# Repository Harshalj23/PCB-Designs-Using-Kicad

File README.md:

# KiCad Projects – Embedded & IoT Hardware Designs

This repository contains a collection of my hardware design projects created using **KiCad**, focused on embedded systems and IoT applications.  
These projects reflect my practical experience in schematic design, PCB layout, and hardware–software integration.

---

## 🛠 Tools & Technologies
- **EDA Tool:** KiCad
- **Microcontrollers:** ESP32, STM32
- **Design Areas:** PCB Design, Schematic Capture, Embedded Hardware
- **Protocols:** UART, SPI, I2C, MQTT, HTTP

---

## 📂 Projects Included
Each folder in this repository represents a complete KiCad project, including schematics, PCB layouts, and supporting files.

Examples:
- **Power Supply Board**
- **IoT Sensor Node**
- **Motor Driver Module**

---

## 🎯 Objectives
- Practice and improve professional PCB design workflow
- Build real-world embedded hardware
- Maintain a clean hardware project portfolio

---

## 🧪 Status
These designs are part of my continuous learning and development in the embedded & IoT domain.  
Updates and improvements are added regularly.

---

## 📬 Contact
**Harshal Jaiswal**  
IoT & Embedded Systems Engineer  
📧 harshaljaiswal055@gmail.com  
🔗 [LinkedIn](https://linkedin.com/in/harshalj67)  
🔗 [GitHub](https://github.com/Harshalj23)

---

Feel free to explore, review, or suggest improvements.

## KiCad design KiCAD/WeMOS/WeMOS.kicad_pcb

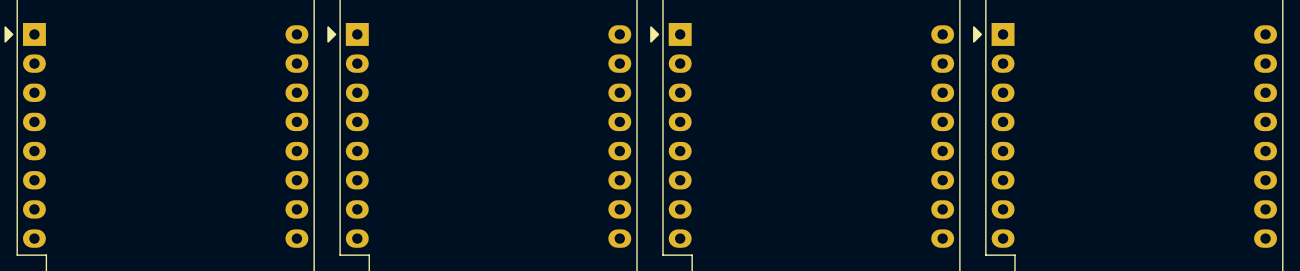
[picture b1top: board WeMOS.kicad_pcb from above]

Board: 2 copper layers, 4 parts (0 on the bottom side), 16 nets, no tracks yet.

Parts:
U1, U2, U3, U4: WEMOS_D1_mini; WEMOS_D1_mini_light

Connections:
unnamed: U1.16 (TX), U2.16 (TX), U3.16 (TX), U4.16 (TX)
unnamed: U1.15 (RX), U2.15 (RX), U3.15 (RX), U4.15 (RX)
unnamed: U1.14 (SCL/D1), U2.14 (SCL/D1), U3.14 (SCL/D1), U4.14 (SCL/D1)
unnamed: U1.13 (SDA/D2), U2.13 (SDA/D2), U3.13 (SDA/D2), U4.13 (SDA/D2)
unnamed: U1.12 (D3), U2.12 (D3), U3.12 (D3), U4.12 (D3)
unnamed: U1.11 (D4), U2.11 (D4), U3.11 (D4), U4.11 (D4)
unnamed: U1.10 (GND), U2.10 (GND), U3.10 (GND), U4.10 (GND)
unnamed: U1.9 (5V), U2.9 (5V), U3.9 (5V), U4.9 (5V)
unnamed: U1.1 (~RST), U2.1 (~RST), U3.1 (~RST), U4.1 (~RST)
unnamed: U1.2 (A0), U2.2 (A0), U3.2 (A0), U4.2 (A0)
unnamed: U1.3 (D0), U2.3 (D0), U3.3 (D0), U4.3 (D0)
unnamed: U1.4 (SCK/D5), U2.4 (SCK/D5), U3.4 (SCK/D5), U4.4 (SCK/D5)
unnamed: U1.5 (MISO/D6), U2.5 (MISO/D6), U3.5 (MISO/D6), U4.5 (MISO/D6)
unnamed: U1.6 (MOSI/D7), U2.6 (MOSI/D7), U3.6 (MOSI/D7), U4.6 (MOSI/D7)
unnamed: U1.7 (CS/D8), U2.7 (CS/D8), U3.7 (CS/D8), U4.7 (CS/D8)
unnamed: U1.8 (3V3), U2.8 (3V3), U3.8 (3V3), U4.8 (3V3)

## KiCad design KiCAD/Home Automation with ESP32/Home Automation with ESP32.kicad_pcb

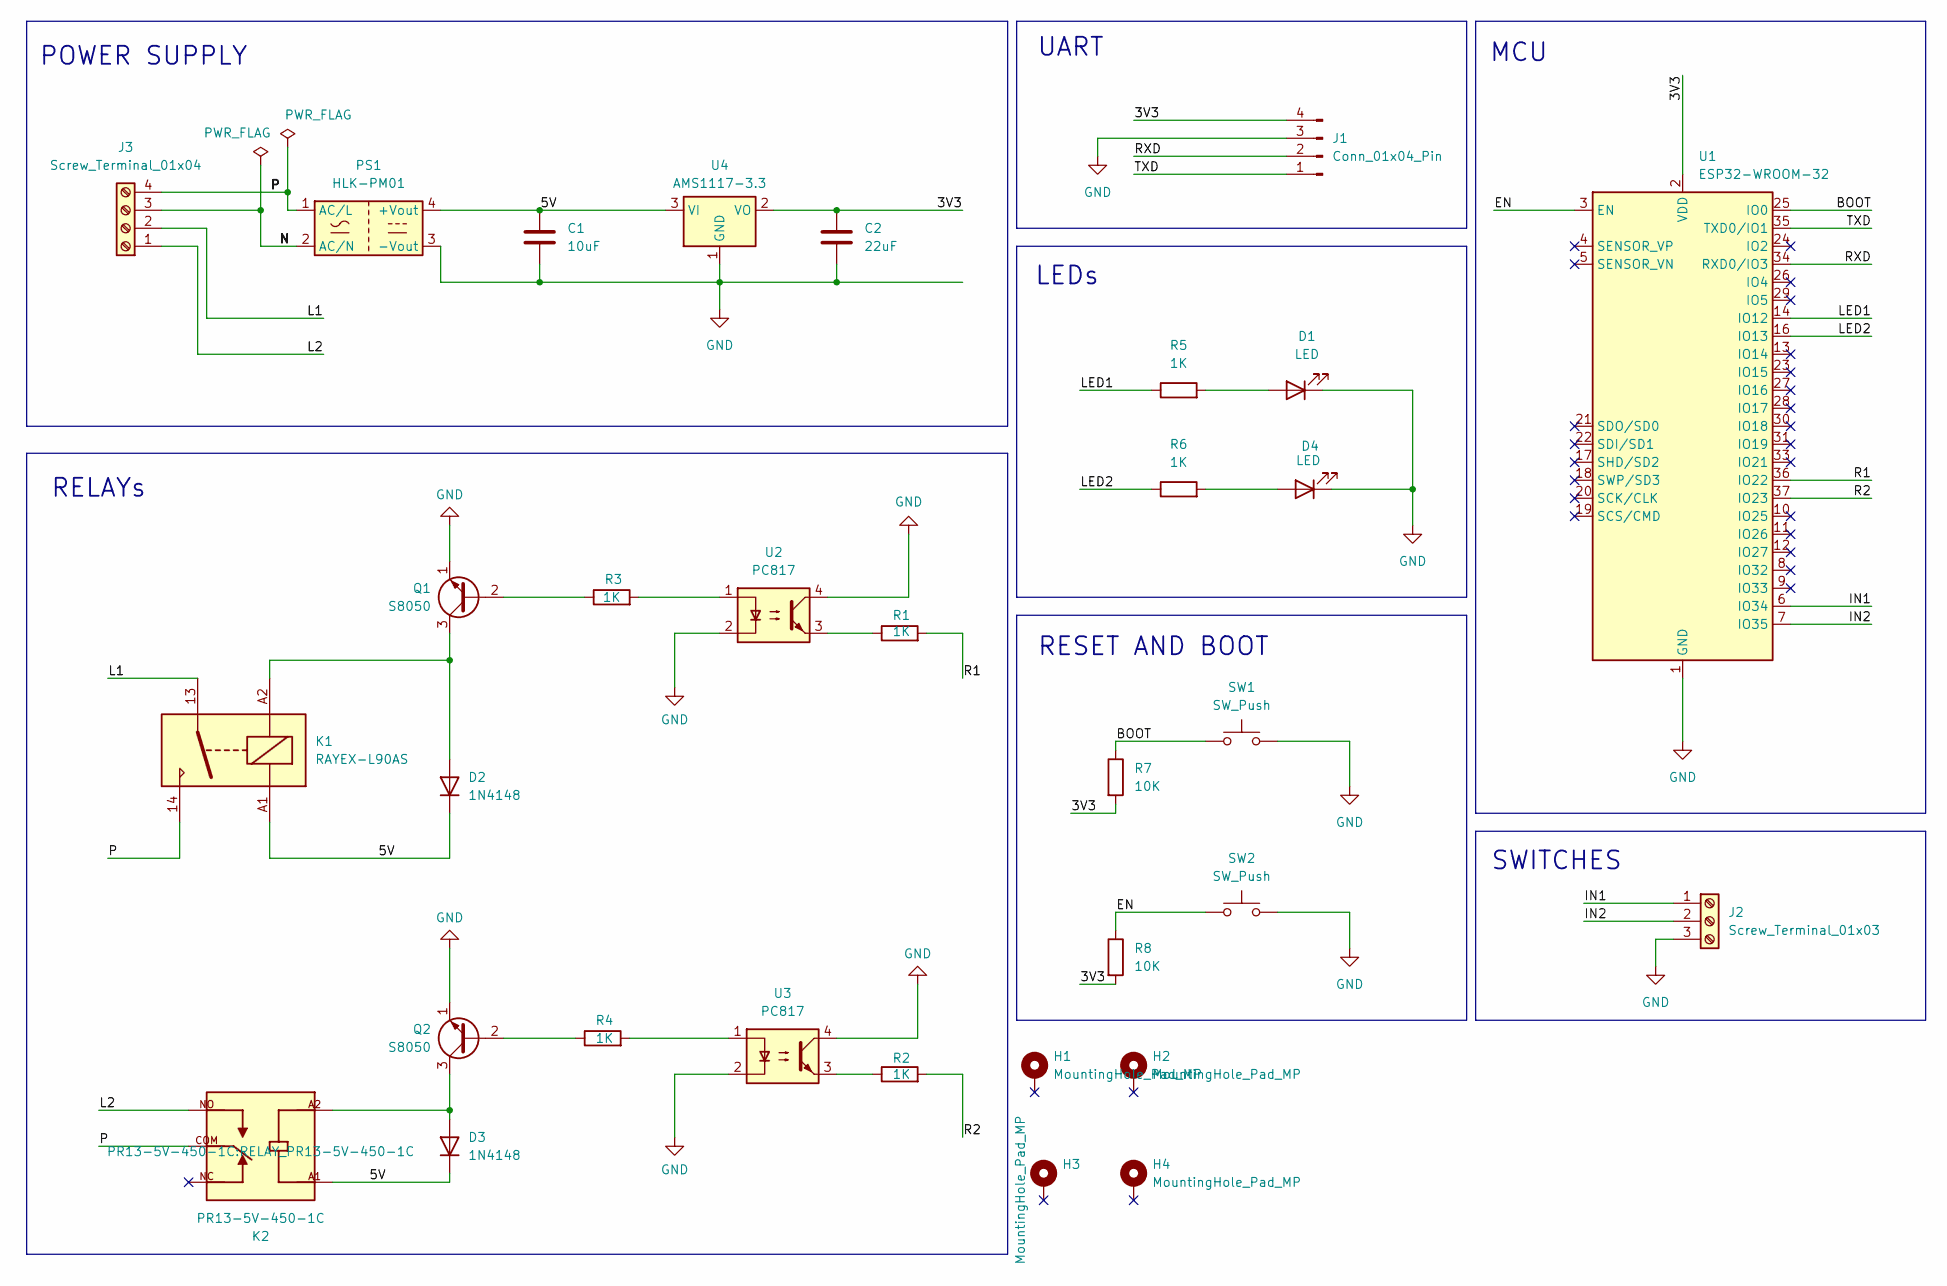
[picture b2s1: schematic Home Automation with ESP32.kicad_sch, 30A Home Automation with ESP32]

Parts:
C1: 10uF; C_0805_2012Metric
C2: 22uF; C_0805_2012Metric
D1, D4: LED; LED_0805_2012Metric
D2, D3: 1N4148; D_DO-35_SOD27_P7.62mm_Horizontal
H1, H2, H3, H4: MountingHole_Pad_MP; MountingHole_2.7mm_M2.5_Pad_Via
J1: Conn_01x04_Pin; PinHeader_1x04_P2.54mm_Vertical
J2: Screw_Terminal_01x03; TerminalBlock_Phoenix_MKDS-1,5-3-5.08_1x03_P5.08mm_Horizont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
J3: Screw_Terminal_01x04; TerminalBlock_Phoenix_MKDS-1,5-4-5.08_1x04_P5.08mm_Horizont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
K1: RAYEX-L90AS; Relay_SPST_RAYEX-L90AS
K2: PR13-5V-450-1C; RELAY_PR13-5V-450-1C; PARTREV 1.0
PS1: HLK-PM01; Converter_ACDC_Hi-Link_HLK-PMxx
Q1, Q2: S8050; TO-92_Inline
R1, R2, R3, R4, R5, R6: 1K; R_0805_2012Metric
R7, R8: 10K; R_0805_2012Metric
SW1, SW2: SW_Push; SW_PUSH_6mm
U1: ESP32-WROOM-32
U2, U3: PC817; DIP-4_W7.62mm
U4: AMS1117-3.3; SOT-223-3_TabPin2

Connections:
/3V3: C2.1, J1.4, R7.2, R8.2, U1.2 (VDD), U4.2 (VO)
/5V: C1.1, D2.1 (K), D3.1 (K), K1.A1, K2.A1, PS1.4 (+Vout), U4.3 (VI)
/BOOT: R7.1, SW1.1, U1.25 (IO0)
/EN: R8.1, SW2.1, U1.3 (EN)
/IN1: J2.1, U1.6 (IO34)
/IN2: J2.2, U1.7 (IO35)
/L1: J3.2, K1.13
/L2: J3.1, K2.NO
/LED1: R5.1, U1.14 (IO12)
/LED2: R6.1, U1.16 (IO13)
/N: J3.3, PS1.2 (AC/N)
/P: J3.4, K1.14, K2.COM, PS1.1 (AC/L)
/R1: R1.2, U1.36 (IO22)
/R2: R2.2, U1.37 (IO23)
/RXD: J1.2, U1.34 (RXD0/IO3)
/TXD: J1.1, U1.35 (TXD0/IO1)
GND: C1.2, C2.2, D1.1 (K), D4.1 (K), J1.3, J2.3, PS1.3 (-Vout), Q1.1 (E), Q2.1 (E), SW1.2, SW2.2, U1.1 (GND), U1.15 (GND), U1.38 (GND), U1.39 (GND), U2.2, U2.4, U3.2, U3.4, U4.1 (GND)
unnamed: D1.2 (A), R5.2
unnamed: D2.2 (A), K1.A2, Q1.3 (C)
unnamed: D3.2 (A), K2.A2, Q2.3 (C)
unnamed: D4.2 (A), R6.2
unnamed: Q1.2 (B), R3.1
unnamed: Q2.2 (B), R4.1
unnamed: R1.1, U2.3
unnamed: R2.1, U3.3
unnamed: R3.2, U2.1
unnamed: R4.2, U3.1

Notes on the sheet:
POWER SUPPLY
UART
SWITCHES
LEDs
MCU
RESET AND BOOT
RELAYs

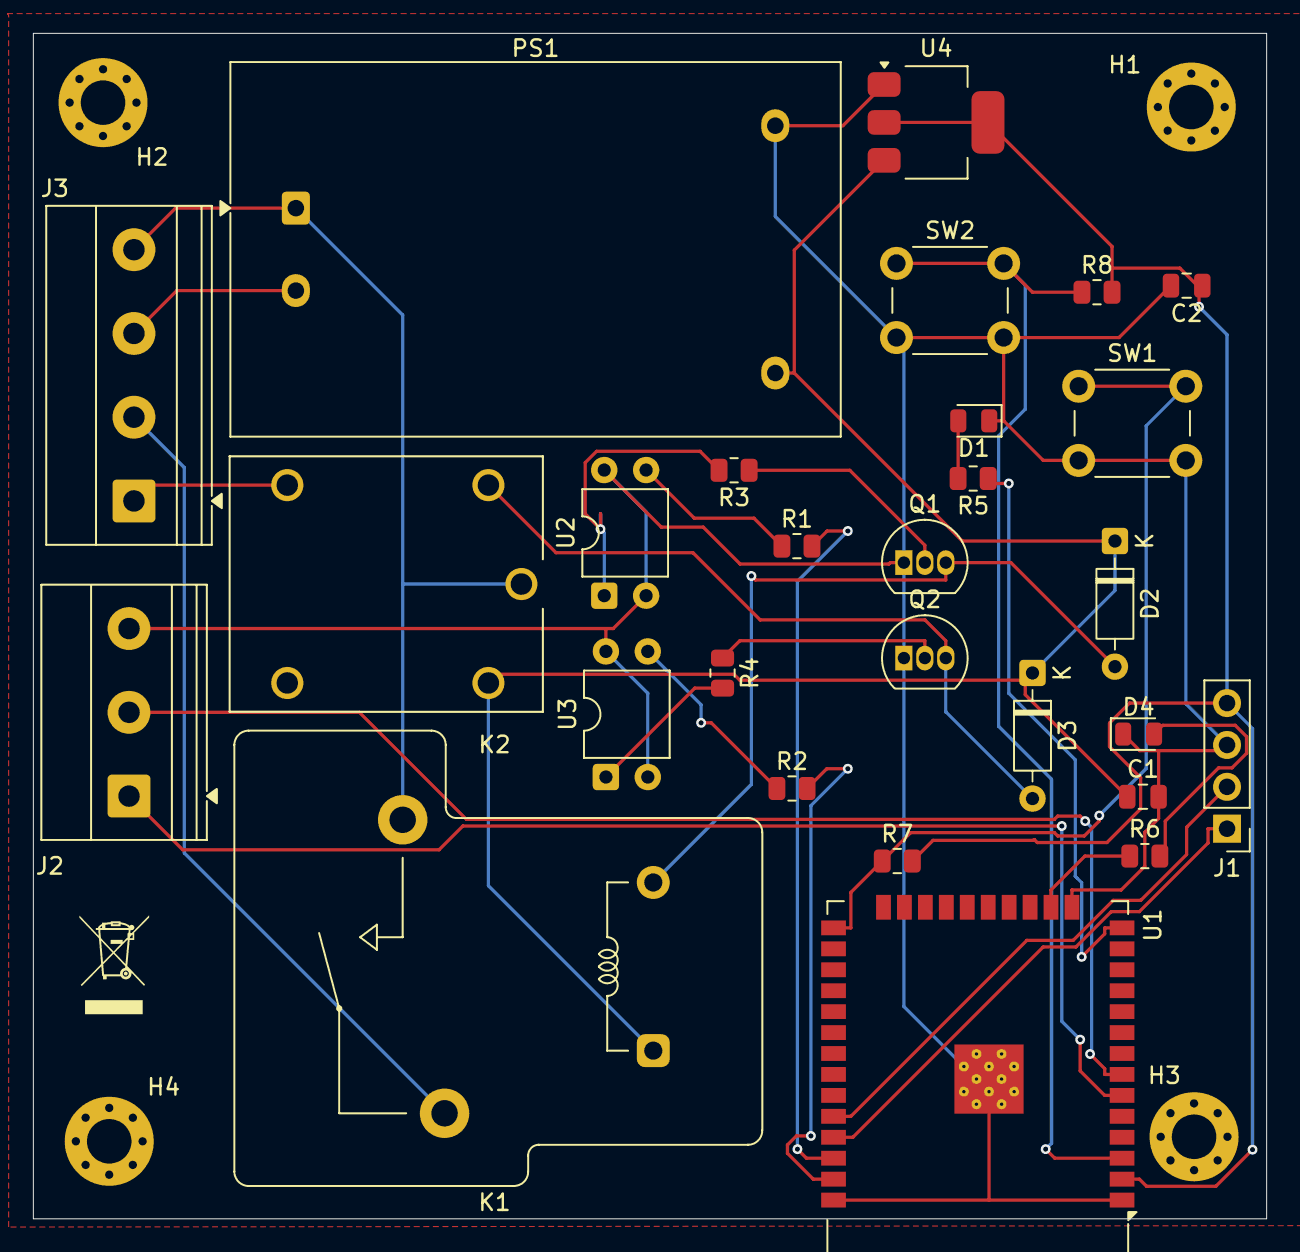
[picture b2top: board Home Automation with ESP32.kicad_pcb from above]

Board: 2 copper layers, 74.8 x 71.9 mm, 32 parts (0 on the bottom side), 27 nets.

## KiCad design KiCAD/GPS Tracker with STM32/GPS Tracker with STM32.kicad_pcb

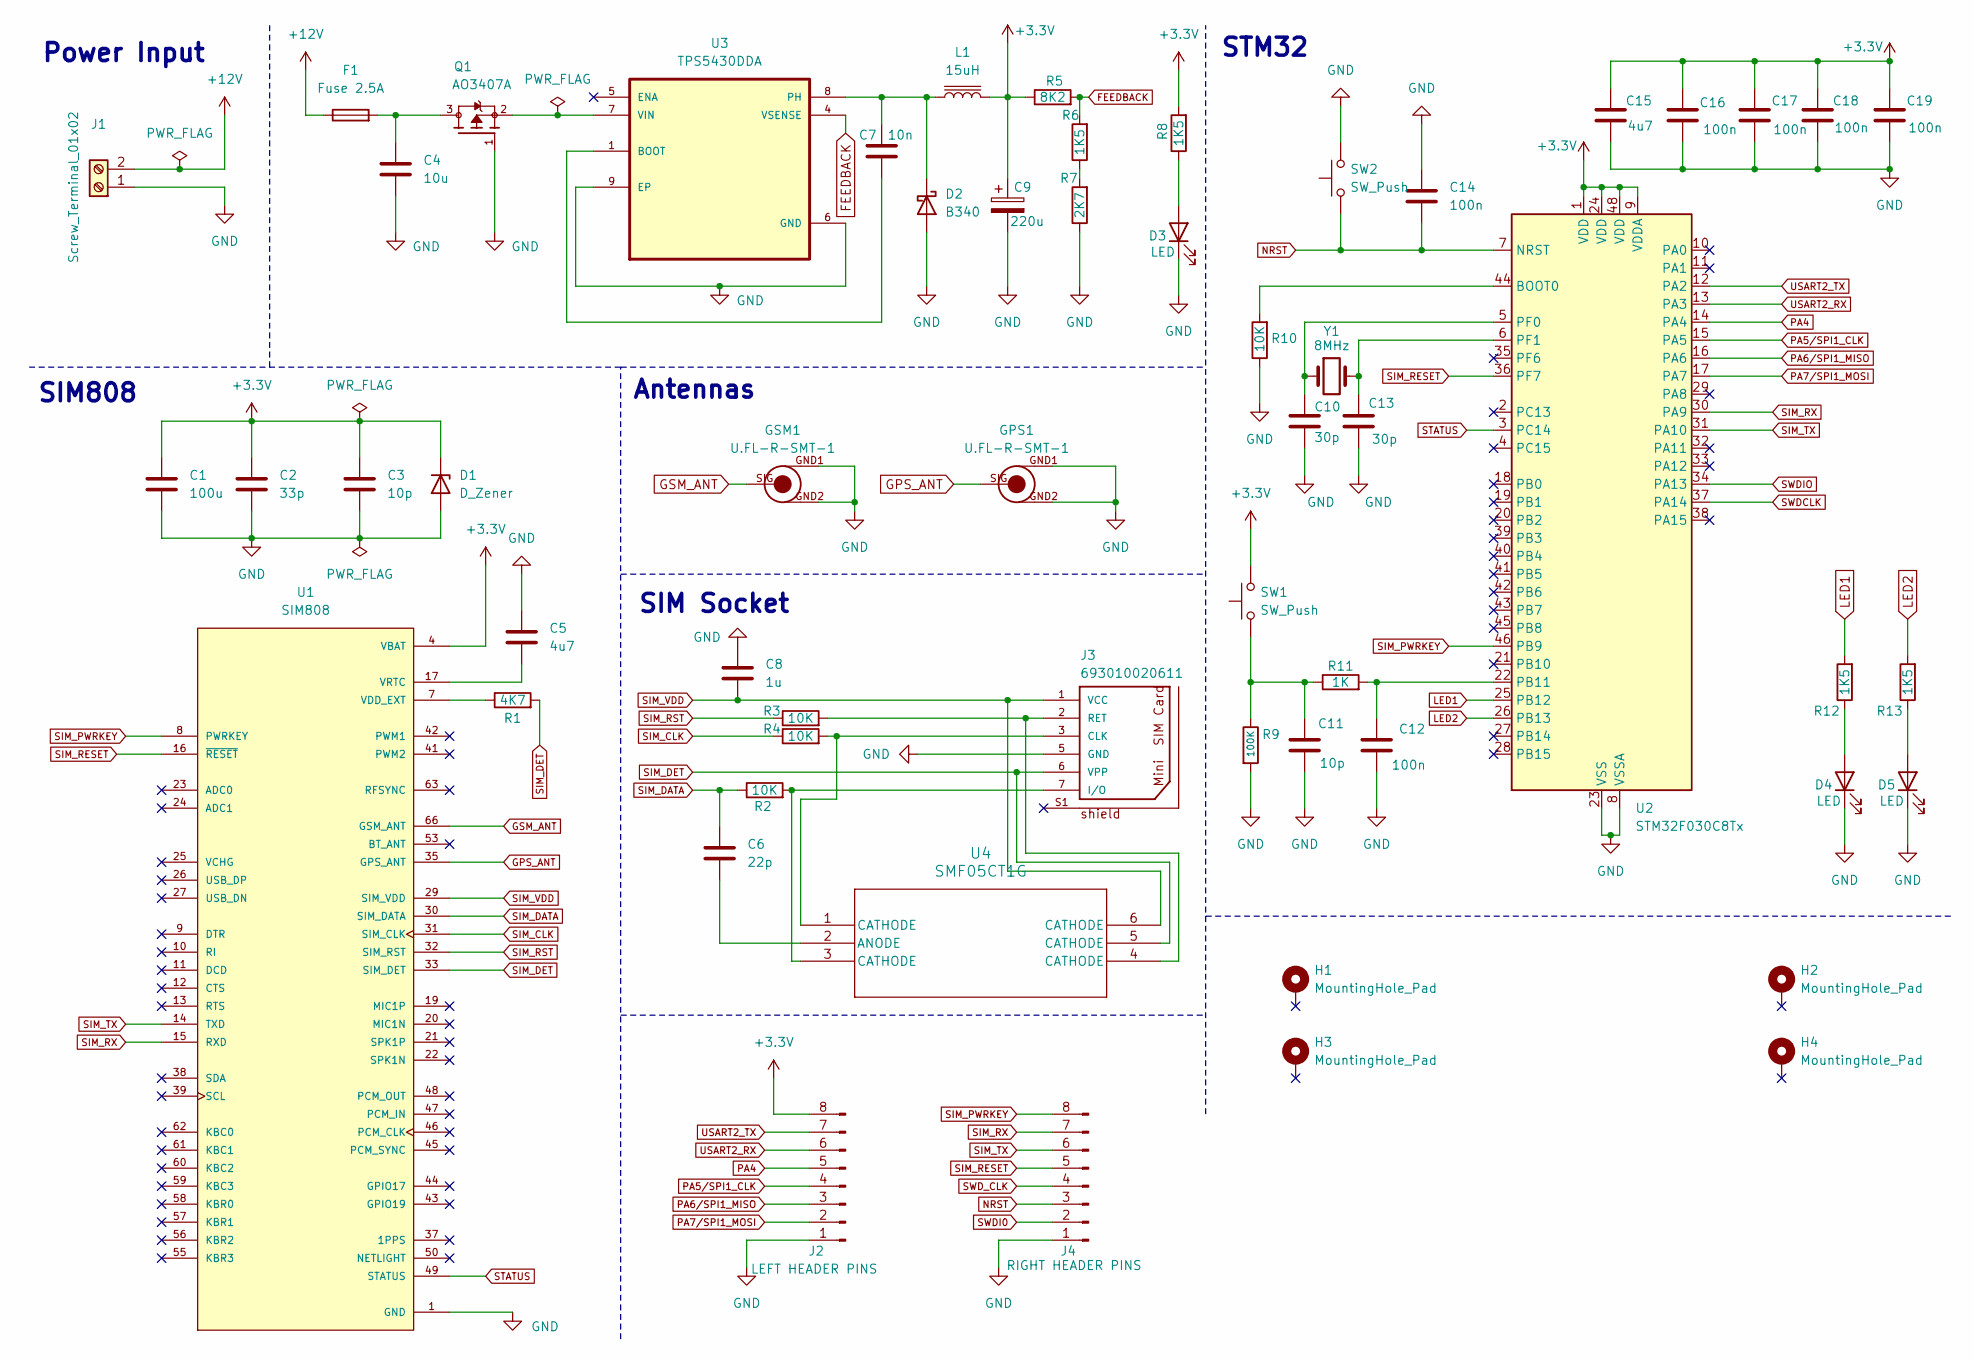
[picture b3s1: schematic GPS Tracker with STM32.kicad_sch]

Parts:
C1: 100u; C_1206_3216Metric
C2: 33p; C_0402_1005Metric
C3, C11: 10p; C_0402_1005Metric
C4: 10u; C_0805_2012Metric
C5, C15: 4u7; C_0201_0603Metric
C6: 22p; C_0402_1005Metric
C7: 10n; C_0201_0603Metric
C8: 1u; C_0402_1005Metric
C9: 220u; CP_EIA-7343-15_Kemet-W
C10, C13: 30p; C_0402_1005Metric
C12, C14, C16, C17, C18, C19: 100n; C_0402_1005Metric
D1: D_Zener; D_0805_2012Metric
D2: B340; D_SMC
D3, D4, D5: LED; LED_0201_0603Metric
F1: Fuse 2.5A; Fuse_0402_1005Metric
GPS1: U.FL-R-SMT-1
GSM1: U.FL-R-SMT-1
H1, H2, H3, H4: MountingHole_Pad; MountingHole_2.2mm_M2_Pad_Via
J1: Screw_Terminal_01x02; TerminalBlock_Phoenix_MKDS-1,5-2_1x02_P5.00mm_Horizontal
J2: LEFT HEADER PINS; PinHeader_1x08_P2.54mm_Vertical
J3: 693010020611
J4: RIGHT HEADER PINS; PinHeader_1x08_P2.54mm_Vertical
L1: 15uH; L_10.4x10.4_H4.8
Q1: AO3407A; SOT95P280X125-3N; PARTREV 5
R1: 4K7; R_0402_1005Metric
R2, R3, R4, R10: 10K; R_0402_1005Metric
R5: 8K2; R_0805_2012Metric
R6, R8, R12, R13: 1K5; R_0805_2012Metric
R7: 2K7; R_0805_2012Metric
R9: 100K; R_0201_0603Metric
R11: 1K; R_0603_1608Metric
SW1, SW2: SW_Push; SW_Push_1P1T_NO_CK_KSC6xxJ
U1: SIM808; XCVR_SIM808; PARTREV 1.03
U2: STM32F030C8Tx; LQFP-48_7x7mm_P0.5mm
U3: TPS5430DDA; VREG_LM5017MR_NOPB
U4: SMF05CT1G; SOT65P210X110-6N
Y1: 8MHz; Crystal_SMD_5032-2Pin_5.0x3.2mm

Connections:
+3.3V: C1.1, C2.1, C3.1, C9.1, C15.1, C16.1, C17.1, C18.1, C19.1, D1.1 (K), J2.8, L1.2, R5.1, R8.2, SW1.2, U1.4 (VBAT), U1.5 (VBAT), U1.6 (VBAT), U2.1 (VDD), U2.9 (VDDA), U2.24 (VDD), U2.48 (VDD)
+12V: F1.1, J1.2
FEEDBACK: R5.2, R6.2, U3.4 (VSENSE)
GND: C1.2, C2.2, C3.2, C4.2, C5.2, C8.1, C9.2, C10.2, C11.2, C12.2, C13.2, C14.1, C15.2, C16.2, C17.2, C18.2, C19.2, D1.2 (A), D2.2 (A), D3.1 (K), D4.1 (K), D5.1 (K), GPS1.GND1, GPS1.GND2, GSM1.GND1, GSM1.GND2, J1.1, J2.1, J3.5 (GND), J4.1, Q1.1, R7.1, R9.2, R10.1, SW2.2, U1.1 (GND), U1.2 (GND), U1.3 (GND), U1.18 (GND), U1.28 (GND), U1.34 (GND), U1.36 (GND), U1.40 (GND), U1.51 (GND), U1.52 (GND), U1.54 (GND), U1.64 (GND), U1.65 (GND), U1.67 (GND), U1.68 (GND), U2.8 (VSSA), U2.23 (VSS), U2.47 (VSS), U3.6 (GND), U3.9 (EP)
GPS_ANT: GPS1.SIG, U1.35 (GPS_ANT)
GSM_ANT: GSM1.SIG, U1.66 (GSM_ANT)
LED1: R12.2, U2.25 (PB12)
LED2: R13.2, U2.26 (PB13)
NRST: C14.2, J4.3, SW2.1, U2.7 (NRST)
unnamed: C4.1, F1.2, Q1.3
unnamed: C11.1, R9.1, R11.1, SW1.1
unnamed: C7.1, D2.1 (K), L1.1, U3.8 (PH)
unnamed: D3.2 (A), R8.1
unnamed: D4.2 (A), R12.1
unnamed: D5.2 (A), R13.1
unnamed: J3.3 (CLK), R4.2, U4.1 (CATHODE)
unnamed: J3.7 (I/O), R2.2, U4.3 (CATHODE)
unnamed: J3.2 (RET), R3.2, U4.4 (CATHODE)
unnamed: R6.1, R7.2
unnamed: R1.1, U1.7 (VDD_EXT)
unnamed: C5.1, U1.17 (VRTC)
unnamed: R10.2, U2.44 (BOOT0)
unnamed: C12.1, R11.2, U2.22 (PB11)
unnamed: C10.1, U2.5 (PF0), Y1.1
unnamed: C13.1, U2.6 (PF1), Y1.2
unnamed: C7.2, U3.1 (BOOT)
unnamed: Q1.2, U3.7 (VIN)
unnamed: C6.2, U4.2 (ANODE)
PA4: J2.5, U2.14 (PA4)
PA5/SPI1_CLK: J2.4, U2.15 (PA5)
PA6/SPI1_MISO: J2.3, U2.16 (PA6)
PA7/SPI1_MOSI: J2.2, U2.17 (PA7)
SIM_CLK: R4.1, U1.31 (SIM_CLK)
SIM_DATA: C6.1, R2.1, U1.30 (SIM_DATA)
SIM_DET: J3.6 (VPP), R1.2, U1.33 (SIM_DET), U4.5 (CATHODE)
SIM_PWRKEY: J4.8, U1.8 (PWRKEY), U2.46 (PB9)
SIM_RESET: J4.5, U1.16 (~RESET), U2.36 (PF7)
SIM_RST: R3.1, U1.32 (SIM_RST)
SIM_RX: J4.7, U1.15 (RXD), U2.30 (PA9)
SIM_TX: J4.6, U1.14 (TXD), U2.31 (PA10)
SIM_VDD: C8.2, J3.1 (VCC), U1.29 (SIM_VDD), U4.6 (CATHODE)
STATUS: U1.49 (STATUS), U2.3 (PC14)
SWDCLK: U2.37 (PA14)
SWDI0: J4.2
SWDIO: U2.34 (PA13)
SWD_CLK: J4.4
USART2_RX: J2.6, U2.13 (PA3)
USART2_TX: J2.7, U2.12 (PA2)

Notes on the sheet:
SIM808
STM32
SIM Socket
Power Input
Antennas

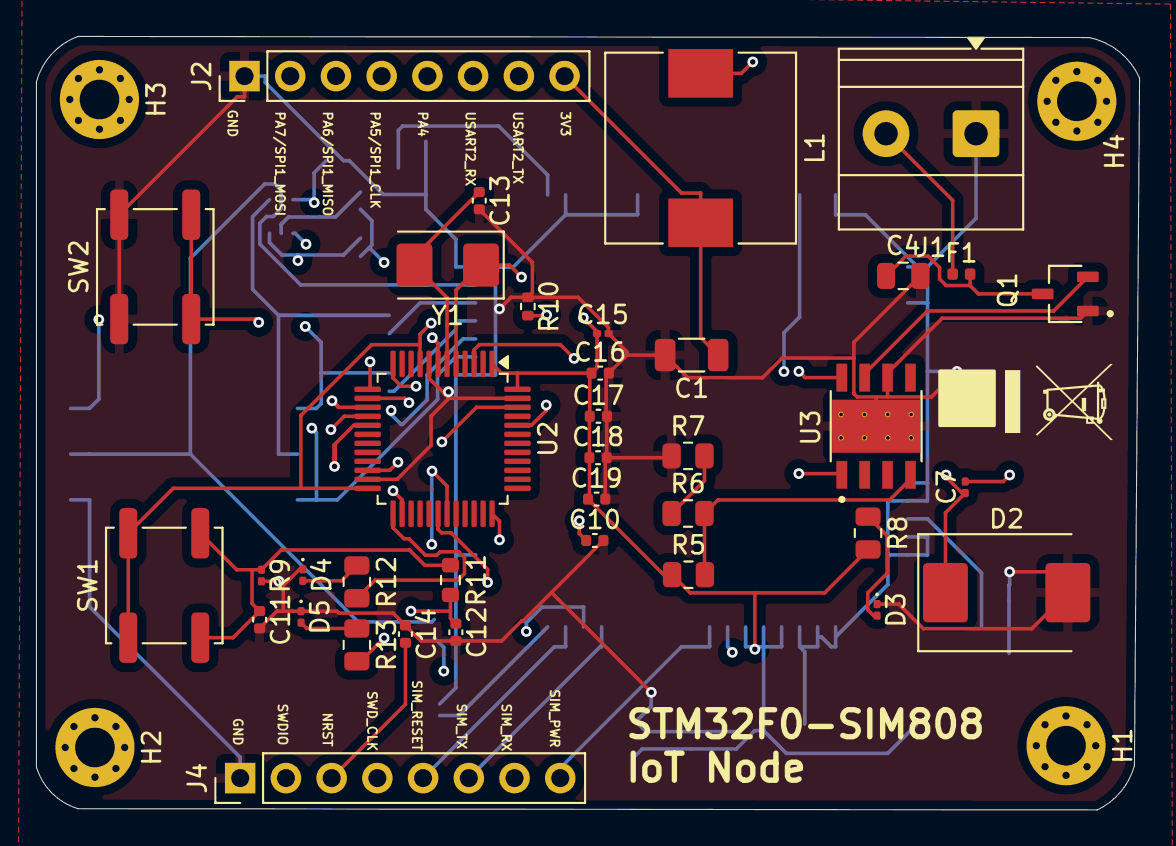
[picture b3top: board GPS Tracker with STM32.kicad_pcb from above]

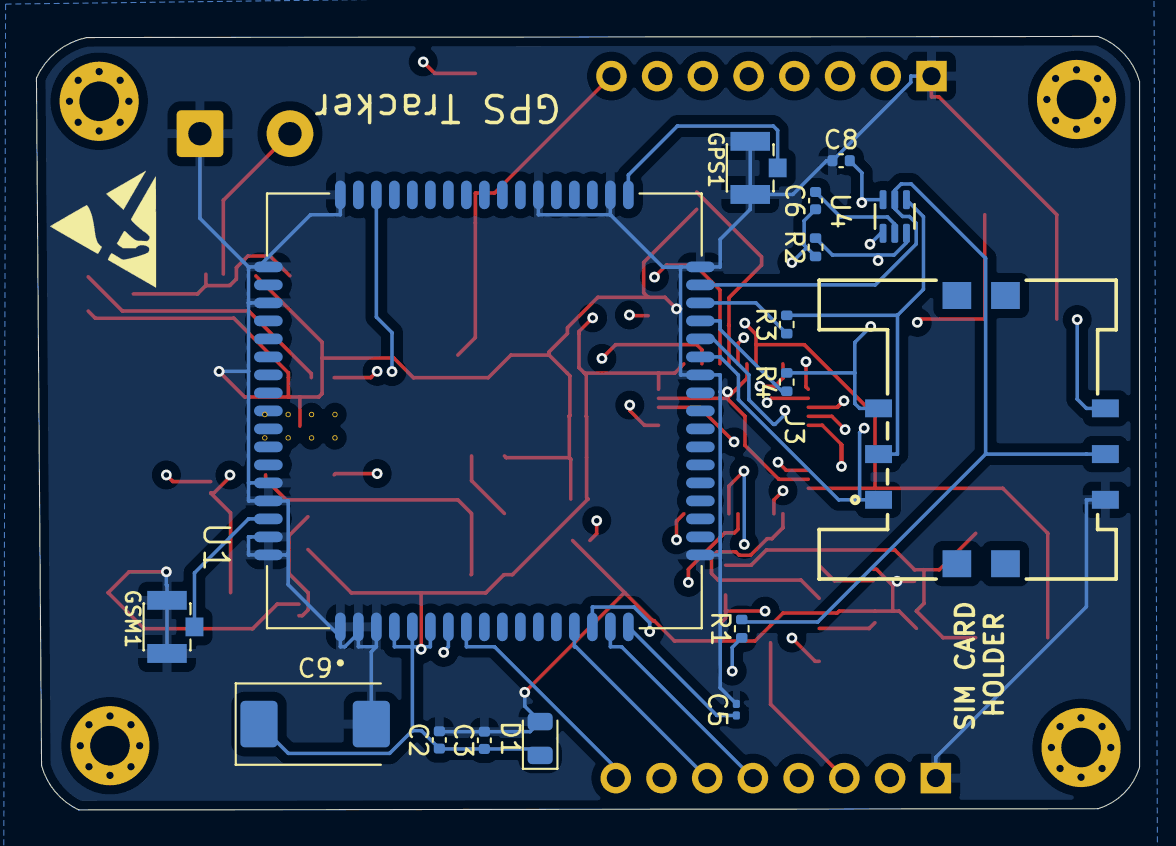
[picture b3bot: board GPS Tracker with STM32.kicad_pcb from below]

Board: 4 copper layers, 61.3 x 43.0 mm, 57 parts (16 on the bottom side), 44 nets.

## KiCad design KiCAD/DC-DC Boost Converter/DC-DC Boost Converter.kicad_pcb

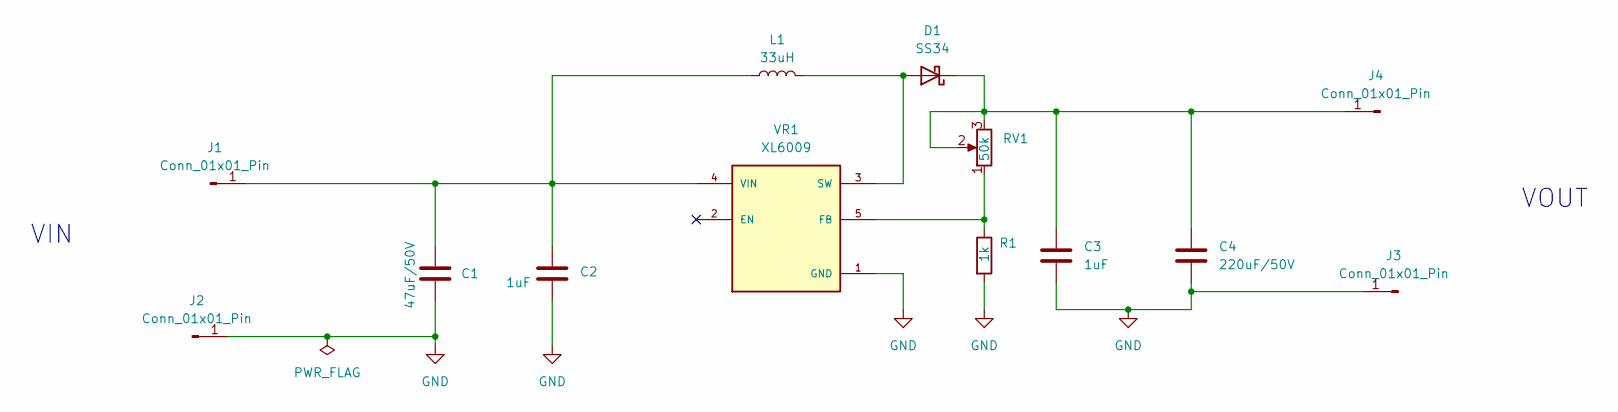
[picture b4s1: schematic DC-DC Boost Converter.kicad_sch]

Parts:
C1: 47uF/50V; C_Radial_D6.3mm_H11.0mm_P2.50mm
C2, C3: 1uF; C_0805_2012Metric
C4: 220uF/50V; C_Radial_D6.3mm_H11.0mm_P2.50mm
D1: SS34; D_SMA
J1, J2, J3, J4: Conn_01x01_Pin; PinHeader_1x01_P2.54mm_Vertical
L1: 33uH; L_12x12mm_H8mm
R1: 1k; R_1206_3216Metric
RV1: 50k; Potentiometer_Bourns_3296W_Vertical
VR1: XL6009; DPAK170P1435X465-6N; PARTREV 1.1

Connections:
GND: C1.2, C2.2, C3.2, C4.2, J2.1, J3.1, R1.2, VR1.1 (GND)
unnamed: D1.2 (A), L1.2, VR1.3 (SW), VR1.6 (SW)
unnamed: C3.1, C4.1, D1.1 (K), J4.1, RV1.2, RV1.3
unnamed: C1.1, C2.1, J1.1, L1.1, VR1.4 (VIN)
unnamed: R1.1, RV1.1, VR1.5 (FB)

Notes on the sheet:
VOUT
VIN

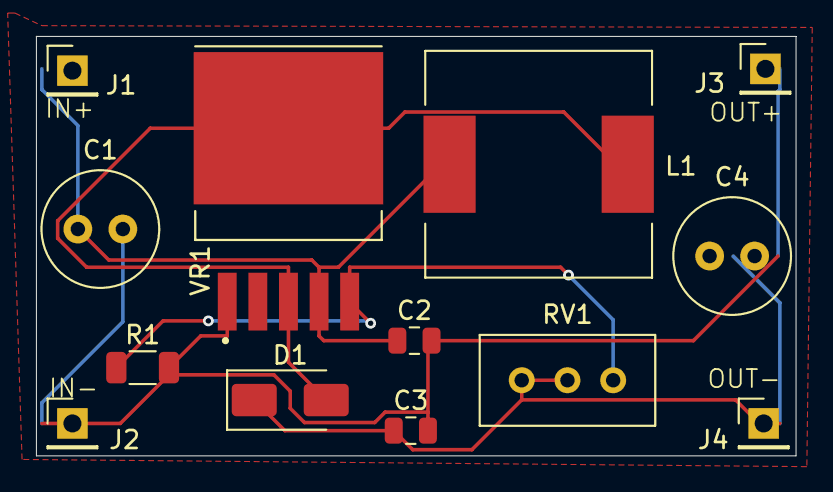
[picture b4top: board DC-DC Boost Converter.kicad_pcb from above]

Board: 2 copper layers, 42.2 x 23.3 mm, 13 parts (0 on the bottom side), 5 nets.

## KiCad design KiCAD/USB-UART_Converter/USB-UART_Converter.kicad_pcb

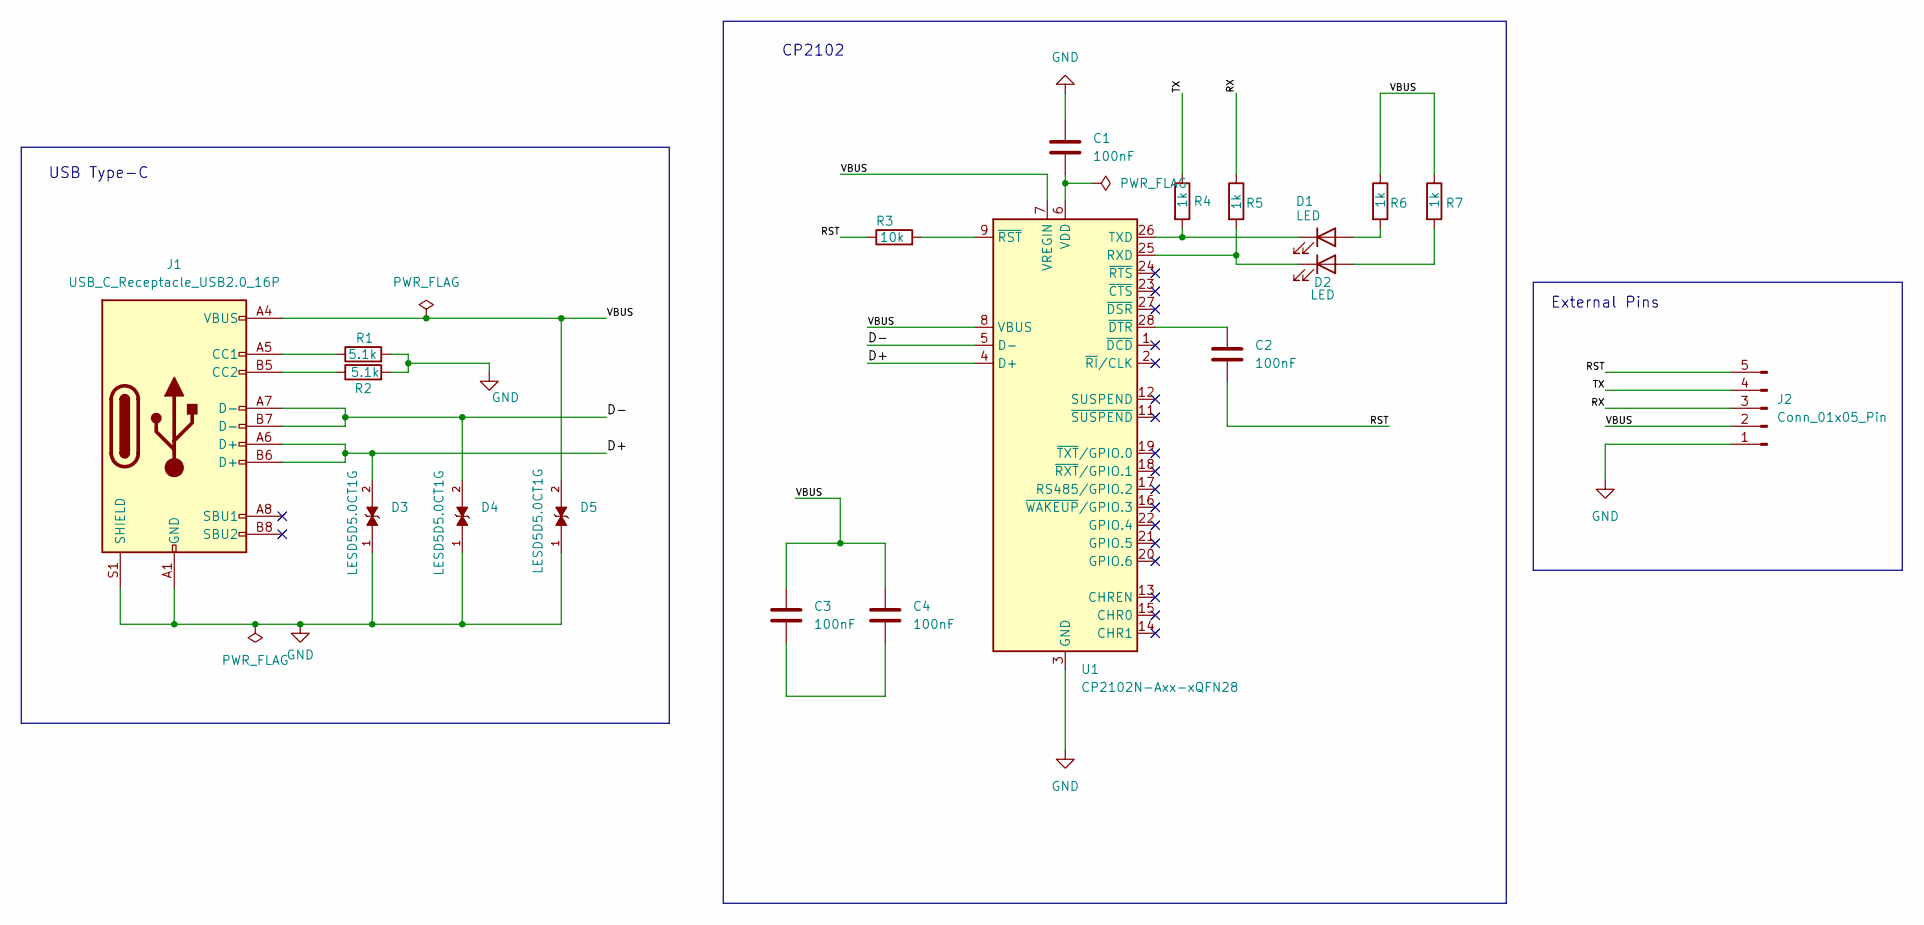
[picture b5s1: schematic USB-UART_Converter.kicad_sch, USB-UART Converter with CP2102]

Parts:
C1, C2, C3, C4: 100nF; C_0201_0603Metric
D1, D2: LED; LED_0201_0603Metric
D3, D4, D5: LESD5D5.0CT1G; TVS_LESD5D5.0CT1G; PARTREV O
J1: USB_C_Receptacle_USB2.0_16P; USB_C_Receptacle_HRO_TYPE-C-31-M-12
J2: Conn_01x05_Pin; PinHeader_1x05_P2.54mm_Horizontal
R1, R2: 5.1k; R_0201_0603Metric
R3: 10k; R_0201_0603Metric
R4, R5, R6, R7: 1k; R_0201_0603Metric
U1: CP2102N-Axx-xQFN28; QFN-28-1EP_5x5mm_P0.5mm_EP3.35x3.35mm

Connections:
/D+: D3.2, J1.A6 (D+), J1.B6 (D+), U1.4 (D+)
/D-: D4.2, J1.A7 (D-), J1.B7 (D-), U1.5 (D-)
/RST: C2.2, J2.5, R3.1
/RX: J2.3, R5.1
/TX: J2.4, R4.1
/VBUS: C3.1, C4.1, D5.2, J1.A4 (VBUS), J1.A9 (VBUS), J1.B4 (VBUS), J1.B9 (VBUS), J2.2, R6.1, R7.1, U1.7 (VREGIN), U1.8 (VBUS)
GND: C1.1, D3.1, D4.1, D5.1, J1.A1 (GND), J1.A12 (GND), J1.B1 (GND), J1.B12 (GND), J1.S1 (SHIELD), J2.1, R1.2, R2.2, U1.3 (GND), U1.29 (GND)
unnamed: C3.2, C4.2
unnamed: D1.2 (A), R6.2
unnamed: D1.1 (K), R4.2, U1.26 (TXD)
unnamed: D2.2 (A), R7.2
unnamed: D2.1 (K), R5.2, U1.25 (RXD)
unnamed: J1.A5 (CC1), R1.1
unnamed: J1.B5 (CC2), R2.1
unnamed: C1.2, U1.6 (VDD)
unnamed: C2.1, U1.28 (~DTR)
unnamed: R3.2, U1.9 (~RST)

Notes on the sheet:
USB Type-C
CP2102
External Pins

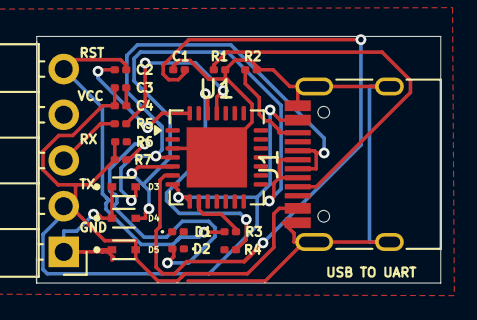
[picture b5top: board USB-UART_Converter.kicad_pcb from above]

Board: 2 copper layers, 22.4 x 13.7 mm, 19 parts (0 on the bottom side), 17 nets.

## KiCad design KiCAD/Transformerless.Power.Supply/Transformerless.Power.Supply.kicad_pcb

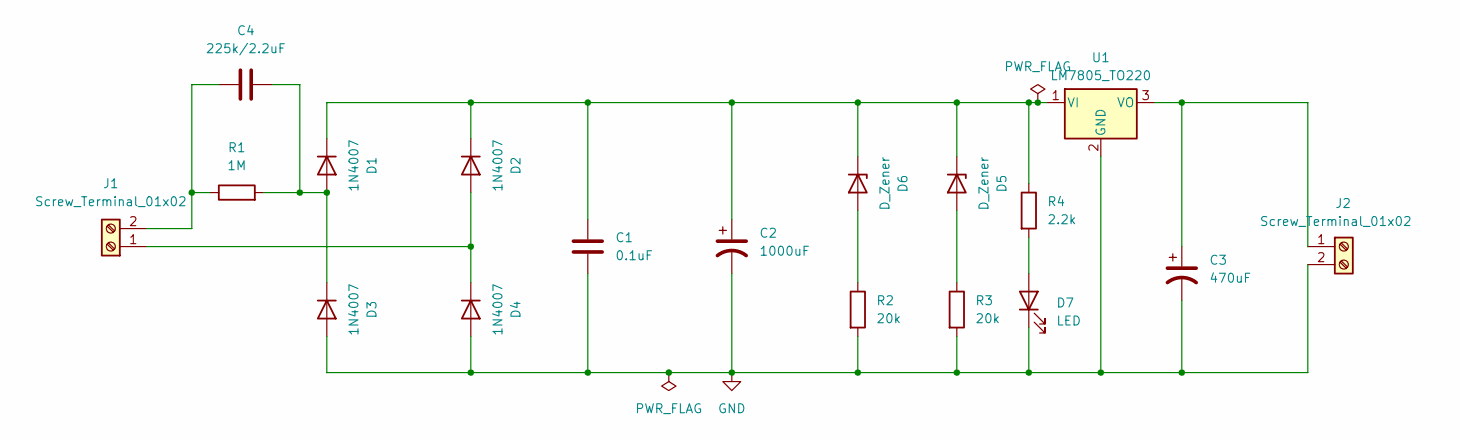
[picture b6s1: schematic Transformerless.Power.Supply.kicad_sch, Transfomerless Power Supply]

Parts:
C1: 0.1uF; C_Disc_D4.7mm_W2.5mm_P5.00mm
C2: 1000uF; CP_Radial_D10.0mm_P5.00mm
C3: 470uF; CP_Radial_D10.0mm_P3.80mm
C4: 225k/2.2uF; C_Rect_L18.0mm_W6.0mm_P15.00mm_FKS3_FKP3
D1, D2, D3, D4: 1N4007; D_DO-41_SOD81_P10.16mm_Horizontal
D5, D6: D_Zener; D_A-405_P7.62mm_Horizontal
D7: LED; LED_D5.0mm
J1, J2: Screw_Terminal_01x02; TerminalBlock_Phoenix_MKDS-1,5-2-5.08_1x02_P5.08mm_Horizont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
R1: 1M; R_Axial_DIN0207_L6.3mm_D2.5mm_P7.62mm_Horizontal
R2, R3: 20k; R_Axial_DIN0207_L6.3mm_D2.5mm_P7.62mm_Horizontal
R4: 2.2k; R_Axial_DIN0207_L6.3mm_D2.5mm_P7.62mm_Horizontal
U1: LM7805_TO220; TO-220-3_Vertical

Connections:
GND: C1.2, C2.2, C3.2, D3.2 (A), D4.2 (A), D7.1 (K), J2.2, R2.2, R3.2, U1.2 (GND)
unnamed: C4.2, D1.2 (A), D3.1 (K), R1.2
unnamed: C1.1, C2.1, D1.1 (K), D2.1 (K), D5.1 (K), D6.1 (K), R4.1, U1.1 (VI)
unnamed: D2.2 (A), D4.1 (K), J1.1
unnamed: D5.2 (A), R3.1
unnamed: D6.2 (A), R2.1
unnamed: D7.2 (A), R4.2
unnamed: C4.1, J1.2, R1.1
unnamed: C3.1, J2.1, U1.3 (VO)

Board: 2 copper layers, 18 parts (0 on the bottom side), 9 nets, no tracks yet.

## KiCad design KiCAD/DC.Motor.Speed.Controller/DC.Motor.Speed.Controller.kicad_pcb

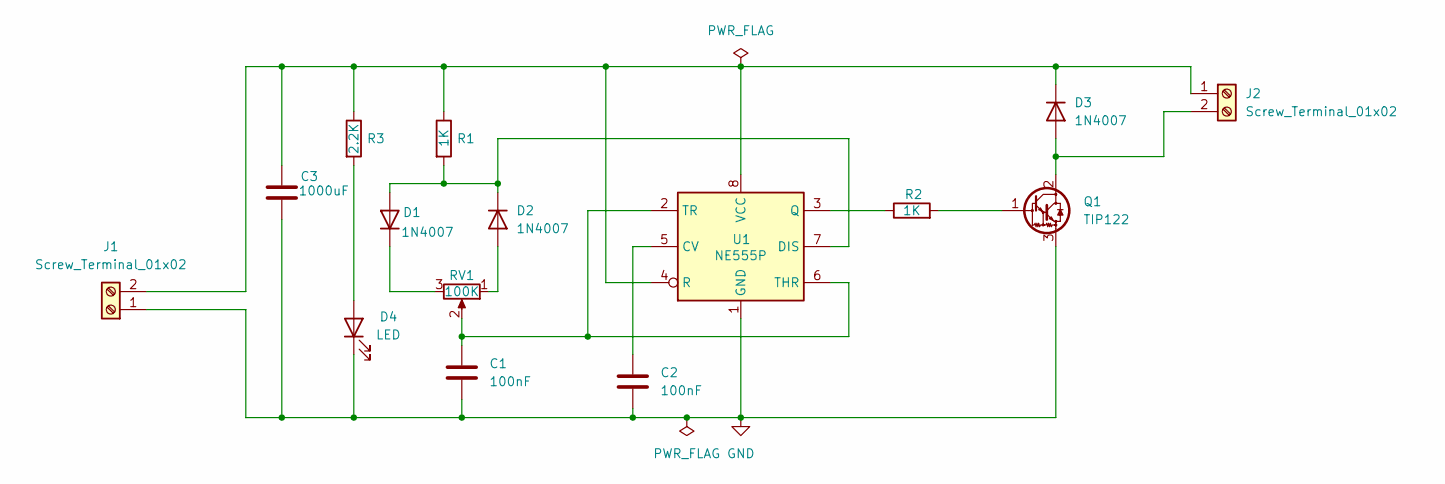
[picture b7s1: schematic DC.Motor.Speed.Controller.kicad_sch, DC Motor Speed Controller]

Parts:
C1, C2: 100nF; C_Disc_D4.7mm_W2.5mm_P5.00mm
C3: 1000uF; CP_Radial_D10.0mm_P5.00mm
D1, D2, D3: 1N4007; D_DO-41_SOD81_P10.16mm_Horizontal
D4: LED; LED_1206_3216Metric_Pad1.42x1.75mm_HandSolder
J1, J2: Screw_Terminal_01x02; TerminalBlock_Phoenix_MKDS-1,5-2_1x02_P5.00mm_Horizontal
Q1: TIP122; TO-220-3_Vertical
R1, R2: 1K; R_Axial_DIN0204_L3.6mm_D1.6mm_P7.62mm_Horizontal
R3: 2.2K; R_Axial_DIN0204_L3.6mm_D1.6mm_P7.62mm_Horizontal
RV1: 100K; Potentiometer_Alps_RK163_Single_Horizontal
U1: NE555P; DIP-8_W7.62mm

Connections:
GND: C1.2, C2.2, C3.1, D4.1 (K), J1.1, Q1.3 (E), U1.1 (GND)
unnamed: D1.2 (A), D2.1 (K), R1.2, U1.7 (DIS)
unnamed: D1.1 (K), RV1.3
unnamed: D2.2 (A), RV1.1
unnamed: D3.2 (A), J2.2, Q1.2 (C)
unnamed: C3.2, D3.1 (K), J1.2, J2.1, R1.1, R3.1, U1.4 (R), U1.8 (VCC)
unnamed: D4.2 (A), R3.2
unnamed: Q1.1 (B), R2.2
unnamed: C2.1, U1.5 (CV)
unnamed: R2.1, U1.3 (Q)
unnamed: C1.1, RV1.2, U1.2 (TR), U1.6 (THR)

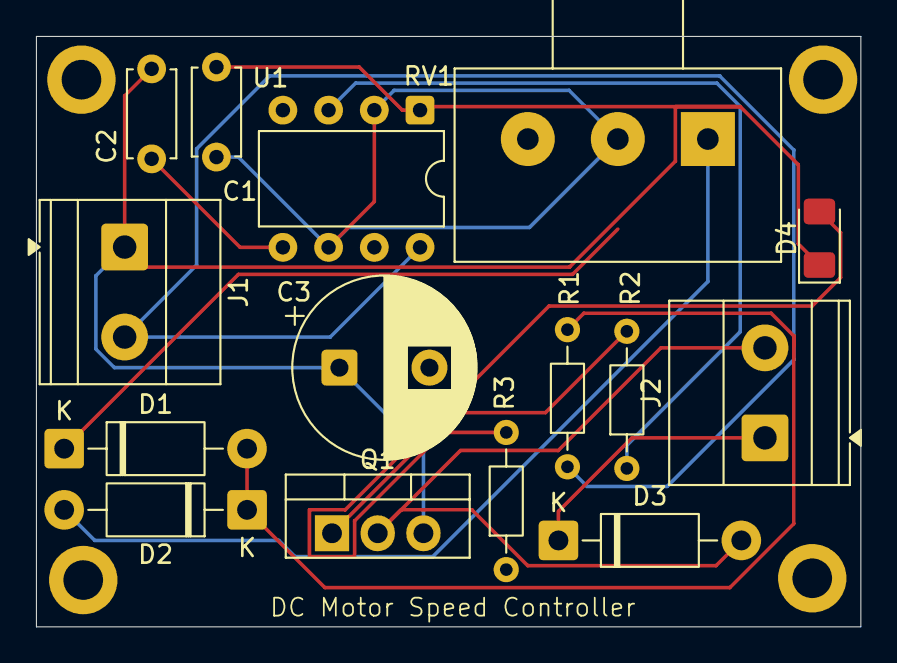
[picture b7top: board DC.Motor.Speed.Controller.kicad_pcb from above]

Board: 2 copper layers, 45.8 x 32.8 mm, 15 parts (0 on the bottom side), 11 nets.

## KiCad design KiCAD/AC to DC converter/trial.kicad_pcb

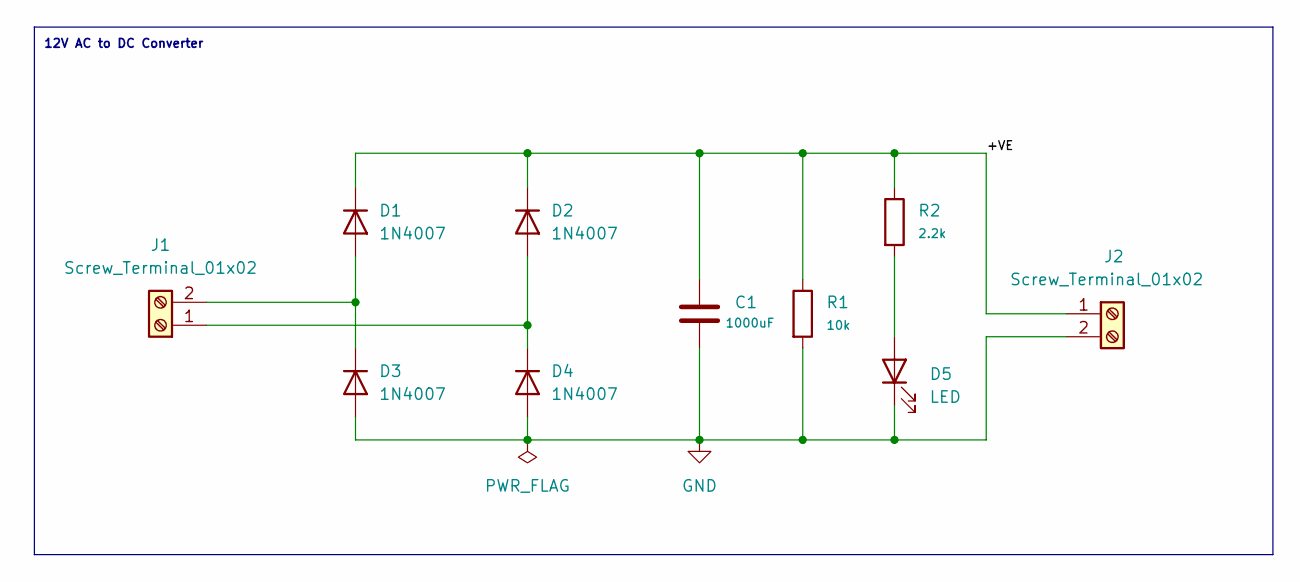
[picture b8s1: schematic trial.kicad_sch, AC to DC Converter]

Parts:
C1: 1000uF; C_Radial_D8.0mm_H11.5mm_P3.50mm
D1, D2, D3, D4: 1N4007; D_DO-41_SOD81_P10.16mm_Horizontal
D5: LED; LED_D5.0mm
J1, J2: Screw_Terminal_01x02; TerminalBlock_Phoenix_MKDS-1,5-2-5.08_1x02_P5.08mm_Horizont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
R1: 10k; R_Axial_DIN0204_L3.6mm_D1.6mm_P7.62mm_Horizontal
R2: 2.2k; R_Axial_DIN0204_L3.6mm_D1.6mm_P7.62mm_Horizontal

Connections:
/+VE: C1.2, D1.1 (K), D2.1 (K), J2.1, R1.1, R2.1
GND: C1.1, D3.2 (A), D4.2 (A), D5.1 (K), J2.2, R1.2
unnamed: D1.2 (A), D3.1 (K), J1.2
unnamed: D2.2 (A), D4.1 (K), J1.1
unnamed: D5.2 (A), R2.2

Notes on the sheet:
12V AC to DC Converter
